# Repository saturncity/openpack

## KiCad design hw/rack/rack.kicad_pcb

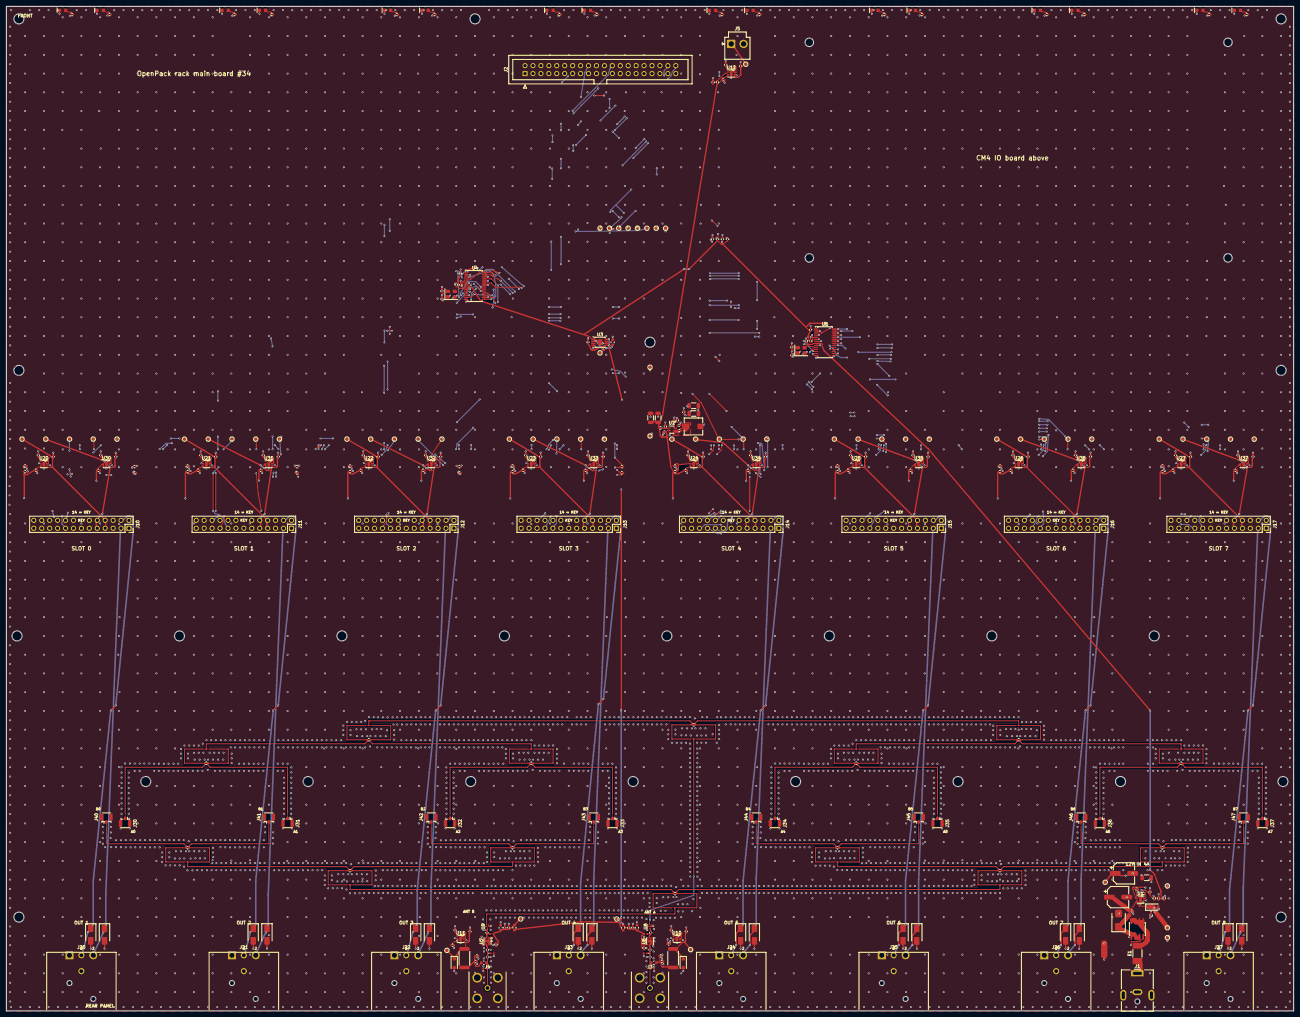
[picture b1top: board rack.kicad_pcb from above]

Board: 4 copper layers, 412.0 x 321.5 mm, 444 parts (0 on the bottom side), 251 nets.

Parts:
C1, C6: 100u 25V; CP_Elec_6.3x5.4
C2, C17, C30, C41, C50, C53, C56, C59, C62, C65, C68, C71, C74, C77, C80, C83, C86, C89, C92, C95: 22n; C_0402_1005Metric
C3, C8, C11, C14, C18, C20, C23, C24, C27, C31, C42, C51, C54, C57, C60, C63, C66, C69, C72, C75, C78, C81, C84, C87, C90, C93, C96: 100n; C_0402_1005Metric
C4, C15, C19, C32, C35, C43, C46, C52, C55, C58, C61, C64, C67, C70, C73, C76, C79, C82, C85, C88, C91, C94, C97: 1u; C_0402_1005Metric
C5, C9, C10: 10u 25V; C_1206_3216Metric
C7: 33n; C_0402_1005Metric
C12, C13: 22u 25V; C_1206_3216Metric
C16, C34, C45: 10u; C_0603_1608Metric
C21, C22, C25, C26: 33p; C_0402_1005Metric
C28, C33, C36, C37, C38, C39, C44, C47, C48, C49: 100p; C_0402_1005Metric
C29, C40: 10n; C_0402_1005Metric
D1: BZT52C12; D_SOD-123
D2: SMBJ12A; D_SMB
D3, D6: ESD103-B1-02EL; D_0402_1005Metric
D4, D7: SMF12A; D_SOD-123F
D5, D8: ESD101-B1-02EL; D_0402_1005Metric
D9, D13, D17, D21, D25, D29, D33, D37: green; LED_LiteOn_LTST-S270
D10, D14, D18, D22, D26, D30, D34, D38: red; LED_LiteOn_LTST-S270
D11, D12, D15, D16, D19, D20, D23, D24, D27, D28, D31, D32, D35, D36, D39, D40: SMAJ58CA; D_SMA
F1: 4A fast; Fuse_Littelfuse-NANO2-451_453
FB1, FB2: 600R@100M; L_0603_1608Metric
H1, H2, H3, H4, H5, H6, H7, H8: MountingHole_3.2mm_M3
HC0, HC1, HC2, HC3: MountingHole_2.7mm_M2.5
HS00, HS01, HS10, HS11, HS20, HS21, HS30, HS31, HS40, HS41, HS50, HS51, HS60, HS61, HS70, HS71: MountingHole_3.2mm_M3
J1: 12V IN; BarrelJack_CUI_PJ-063AH_Horizontal
J2: CM4IO J8; IDC-Header_2x20_P2.54mm_Vertical
J3: ANT A; BNC_TE_5415025-1_RA
J4: ANT B; BNC_TE_5415025-1_RA
J5: CM4IO 12V; JST_VH_B2P-VH_1x02_P3.96mm_Vertical
J10: SLOT 0; PinSocket_2x13_P2.54mm_Key14
J11: SLOT 1; PinSocket_2x13_P2.54mm_Key14
J12: SLOT 2; PinSocket_2x13_P2.54mm_Key14
J13: SLOT 3; PinSocket_2x13_P2.54mm_Key14
J14: SLOT 4; PinSocket_2x13_P2.54mm_Key14
J15: SLOT 5; PinSocket_2x13_P2.54mm_Key14
J16: SLOT 6; PinSocket_2x13_P2.54mm_Key14
J17: SLOT 7; PinSocket_2x13_P2.54mm_Key14
J20: OUT 1; Neutrik_NC3MAH
J21: OUT 2; Neutrik_NC3MAH
J22: OUT 3; Neutrik_NC3MAH
J23: OUT 4; Neutrik_NC3MAH
J24: OUT 5; Neutrik_NC3MAH
J25: OUT 6; Neutrik_NC3MAH
J26: OUT 7; Neutrik_NC3MAH
J27: OUT 8; Neutrik_NC3MAH
J30: RF A0; U.FL_Hirose_U.FL-R-SMT-1_Vertical
J31: RF A1; U.FL_Hirose_U.FL-R-SMT-1_Vertical
J32: RF A2; U.FL_Hirose_U.FL-R-SMT-1_Vertical
J33: RF A3; U.FL_Hirose_U.FL-R-SMT-1_Vertical
J34: RF A4; U.FL_Hirose_U.FL-R-SMT-1_Vertical
J35: RF A5; U.FL_Hirose_U.FL-R-SMT-1_Vertical
J36: RF A6; U.FL_Hirose_U.FL-R-SMT-1_Vertical
J37: RF A7; U.FL_Hirose_U.FL-R-SMT-1_Vertical
J40: RF B0; U.FL_Hirose_U.FL-R-SMT-1_Vertical
J41: RF B1; U.FL_Hirose_U.FL-R-SMT-1_Vertical
J42: RF B2; U.FL_Hirose_U.FL-R-SMT-1_Vertical
J43: RF B3; U.FL_Hirose_U.FL-R-SMT-1_Vertical
J44: RF B4; U.FL_Hirose_U.FL-R-SMT-1_Vertical
J45: RF B5; U.FL_Hirose_U.FL-R-SMT-1_Vertical
J46: RF B6; U.FL_Hirose_U.FL-R-SMT-1_Vertical
J47: RF B7; U.FL_Hirose_U.FL-R-SMT-1_Vertical
L1: 6.8u; L_Bourns_SRP5030T
L2, L4: 39n; L_0603_1608Metric
L3, L5: 18n; L_0402_1005Metric
NT1: GND-CHASSIS; NetTie-2_SMD_Pad2.0mm
Q1: AO4407A; SOIC-8_3.9x4.9mm_P1.27mm
R1, R3, R5, R11, R14, R16, R19, R32, R44, R52, R60, R68, R76, R82, R88, R94: 10k; R_0402_1005Metric
R2, R10, R43, R51, R59, R67, R75, R81, R87, R93: 73.2k; R_0402_1005Metric
R4: 576; R_0402_1005Metric
R6: 511k; R_0402_1005Metric
R7: 88.7k; R_0402_1005Metric
R8: 53.6k; R_0402_1005Metric
R9: 10.2k; R_0402_1005Metric
R12: 1.37k; R_0402_1005Metric
R13, R15, R48, R56, R64, R72: 1k; R_0402_1005Metric
R17, R30: 1; R_2512_6332Metric
R18, R31: 100k; R_0402_1005Metric
R20, R33, R45, R46, R53, R54, R61, R62, R69, R70, R77, R78, R83, R84, R89, R90, R95, R96: 4.42k; R_0402_1005Metric
R21, R34: 0; R_0402_1005Metric
R22, R35: 5.1k; R_0402_1005Metric
R23, R24, R25, R26, R27, R28, R29, R36, R37, R38, R39, R40, R41, R42, R47, R55, R63, R71: 100; R_0402_1005Metric
R49, R50, R57, R58, R65, R66, R73, R74, R79, R80, R85, R86, R91, R92, R97, R98: 560; R_0402_1005Metric
TL1, TL2, TL3, TL4, TL5, TL6, TL7, TL8, TL9, TL10, TL11, TL12, TL13, TL14, TL15, TL16, TL17, TL18, TL19, TL20, TL21, TL22, TL23, TL24, TL25, TL26, TL27, TL28: 70R7 L/4 18.02mm w0.170; Microstrip_NetTie
TL29, TL30, TL31, TL32, TL33, TL34, TL35, TL36, TL37, TL38, TL39, TL40, TL41, TL42, TL43, TL44: 50R feed; Microstrip_NetTie
TP1: +12V_PROT; TestPoint_Pad_D1.0mm
TP2: +12V_BUS; TestPoint_Pad_D1.0mm
TP3: +5V; TestPoint_Pad_D1.0mm
TP4: +3V3; TestPoint_Pad_D1.0mm
TP5: +12V_HOST; TestPoint_Pad_D1.0mm
TP6: HOST_GPIO6; TestPoint_Pad_D1.0mm
TP7, TP8, TP16: GND; TestPoint_Pad_D1.0mm
TP9: HOST_GPIO21; TestPoint_Pad_D1.0mm
TP10: HOST_GPIO20; TestPoint_Pad_D1.0mm
TP11: HOST_GPIO19; TestPoint_Pad_D1.0mm
TP12: HOST_GPIO18; TestPoint_Pad_D1.0mm
TP13: HOST_GPIO17; TestPoint_Pad_D1.0mm
TP14: HOST_GPIO24; TestPoint_Pad_D1.0mm
TP15: HOST_GPIO25; TestPoint_Pad_D1.0mm
TP17: BIAS_A_DC; TestPoint_Pad_D1.0mm
TP18: +5V_LNA_A; TestPoint_Pad_D1.0mm
TP19: BIAS_B_DC; TestPoint_Pad_D1.0mm
TP20: +5V_LNA_B; TestPoint_Pad_D1.0mm
TP21: +12V_S0; TestPoint_Pad_D1.0mm
TP22: +5V_S0; TestPoint_Pad_D1.0mm
TP23: S0_BP_UART_TX; TestPoint_Pad_D1.0mm
TP24: S0_BP_UART_RX; TestPoint_Pad_D1.0mm
TP25: S0_BP_nRESET; TestPoint_Pad_D1.0mm
TP26: +12V_S1; TestPoint_Pad_D1.0mm
TP27: +5V_S1; TestPoint_Pad_D1.0mm
TP28: S1_BP_UART_TX; TestPoint_Pad_D1.0mm
TP29: S1_BP_UART_RX; TestPoint_Pad_D1.0mm
TP30: S1_BP_nRESET; TestPoint_Pad_D1.0mm
TP31: +12V_S2; TestPoint_Pad_D1.0mm
TP32: +5V_S2; TestPoint_Pad_D1.0mm
TP33: S2_BP_UART_TX; TestPoint_Pad_D1.0mm
TP34: S2_BP_UART_RX; TestPoint_Pad_D1.0mm
TP35: S2_BP_nRESET; TestPoint_Pad_D1.0mm
TP36: +12V_S3; TestPoint_Pad_D1.0mm
TP37: +5V_S3; TestPoint_Pad_D1.0mm
TP38: S3_BP_UART_TX; TestPoint_Pad_D1.0mm
TP39: S3_BP_UART_RX; TestPoint_Pad_D1.0mm
TP40: S3_BP_nRESET; TestPoint_Pad_D1.0mm
TP41: +12V_S4; TestPoint_Pad_D1.0mm
TP42: +5V_S4; TestPoint_Pad_D1.0mm
TP43: S4_BP_UART_TX; TestPoint_Pad_D1.0mm
TP44: S4_BP_UART_RX; TestPoint_Pad_D1.0mm
TP45: S4_BP_nRESET; TestPoint_Pad_D1.0mm
TP46: +12V_S5; TestPoint_Pad_D1.0mm
TP47: +5V_S5; TestPoint_Pad_D1.0mm
TP48: S5_BP_UART_TX; TestPoint_Pad_D1.0mm
TP49: S5_BP_UART_RX; TestPoint_Pad_D1.0mm
TP50: S5_BP_nRESET; TestPoint_Pad_D1.0mm
TP51: +12V_S6; TestPoint_Pad_D1.0mm
TP52: +5V_S6; TestPoint_Pad_D1.0mm
TP53: S6_BP_UART_TX; TestPoint_Pad_D1.0mm
TP54: S6_BP_UART_RX; TestPoint_Pad_D1.0mm
TP55: S6_BP_nRESET; TestPoint_Pad_D1.0mm
TP56: +12V_S7; TestPoint_Pad_D1.0mm
TP57: +5V_S7; TestPoint_Pad_D1.0mm
TP58: S7_BP_UART_TX; TestPoint_Pad_D1.0mm
TP59: S7_BP_UART_RX; TestPoint_Pad_D1.0mm
TP60: S7_BP_nRESET; TestPoint_Pad_D1.0mm
U1, U10, U11, U12, U20, U21, U22, U23, U24, U25, U26, U27: TPS259541DSGR; Texas_DSG0008A_WSON-8-1EP_2x2mm_P0.5mm_EP0.9x1.6mm
U2: TPS62933DRLR; SOT-583-8
U3: TLV76733; HVSSOP-8-1EP_3x3mm_P0.65mm_EP1.57x1.89mm
U4, U5: SC16IS752IPW; TSSOP-28_4.4x9.7mm_P0.65mm
U6, U7: QPL9057; DFN-8-1EP_2x2mm_P0.5mm_EP0.9x1.6mm
U8, U9: QPQ1907; Qorvo_QPQ1907_LGA5_1.4x1.2mm_datasheet_land_pattern
U30, U31, U32, U33, U34, U35, U36, U37: TPS259531DSGR; Texas_DSG0008A_WSON-8-1EP_2x2mm_P0.5mm_EP0.9x1.6mm
Y1, Y2: 14.7456M; Crystal_SMD_3225-4Pin_3.2x2.5mm

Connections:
+3V3: C16.1, C23.1, C27.1, R5.1, R13.1, R14.1, R15.1, R16.1, R19.1, R32.1, TP4.1, U3.1, U3.2, U4.8, U5.8
+5V: C12.1, C13.1, C14.1, C15.1, C54.1, C60.1, C66.1, C72.1, C78.1, C84.1, C90.1, C96.1, FB1.1, FB2.1, L1.2, R8.1, TP3.1, U3.5, U3.8, U30.2, U30.3, U30.4, U31.2, U31.3, U31.4, U32.2, U32.3, U32.4, U33.2, U33.3, U33.4, U34.2, U34.3, U34.4, U35.2, U35.3, U35.4, U36.2, U36.3, U36.4, U37.2, U37.3, U37.4
+5V_LNA_A: C34.1, C35.1, C36.1, FB1.2, L3.1, R22.1, TP18.1
+5V_LNA_B: C45.1, C46.1, C47.1, FB2.2, L5.1, R35.1, TP20.1
+5V_S0: C55.1, J10.9, J10.10, TP22.1, U30.5
+5V_S1: C61.1, J11.9, J11.10, TP27.1, U31.5
+5V_S2: C67.1, J12.9, J12.10, TP32.1, U32.5
+5V_S3: C73.1, J13.9, J13.10, TP37.1, U33.5
+5V_S4: C79.1, J14.9, J14.10, TP42.1, U34.5
+5V_S5: C85.1, J15.9, J15.10, TP47.1, U35.5
+5V_S6: C91.1, J16.9, J16.10, TP52.1, U36.5
+5V_S7: C97.1, J17.9, J17.10, TP57.1, U37.5
+12V_BUS: C4.1, C5.1, C6.1, C9.1, C10.1, C11.1, C18.1, C31.1, C42.1, C51.1, C57.1, C63.1, C69.1, C75.1, C81.1, C87.1, C93.1, R2.1, R6.1, R10.1, R43.1, R51.1, R59.1, R67.1, R75.1, R81.1, R87.1, R93.1, TP2.1, U1.5, U2.3, U10.3, U10.4, U11.3, U11.4, U12.3, U12.4, U20.3, U20.4, U21.3, U21.4, U22.3, U22.4, U23.3, U23.4, U24.3, U24.4, U25.3, U25.4, U26.3, U26.4, U27.3, U27.4
+12V_HOST: C19.1, J5.1, TP5.1, U12.5
+12V_IN: F1.1, J1.1
+12V_PROT: C1.1, C3.1, D1.1, D2.1, Q1.1, Q1.2, Q1.3, TP1.1, U1.3, U1.4
+12V_RAW: F1.2, Q1.5, Q1.6, Q1.7, Q1.8
+12V_S0: C52.1, J10.7, J10.8, TP21.1, U20.5
+12V_S1: C58.1, J11.7, J11.8, TP26.1, U21.5
+12V_S2: C64.1, J12.7, J12.8, TP31.1, U22.5
+12V_S3: C70.1, J13.7, J13.8, TP36.1, U23.5
+12V_S4: C76.1, J14.7, J14.8, TP41.1, U24.5
+12V_S5: C82.1, J15.7, J15.8, TP46.1, U25.5
+12V_S6: C88.1, J16.7, J16.8, TP51.1, U26.5
+12V_S7: C94.1, J17.7, J17.8, TP56.1, U27.5
ANT_A: C33.1, D3.1, J3.1, L2.1
ANT_B: C44.1, D6.1, J4.1, L4.1
BIAS_A_DC: C32.1, D4.1, R17.2, TP17.1, U10.5
BIAS_A_RF: C28.1, C29.1, L2.2, R17.1
BIAS_B_DC: C43.1, D7.1, R30.2, TP19.1, U11.5
BIAS_B_RF: C39.1, C40.1, L4.2, R30.1
BUCK_BST: C8.1, U2.6
BUCK_EN: R6.2, R7.1, U2.2
BUCK_FB: R8.2, R9.1, U2.8
BUCK_SS: C7.1, U2.7
BUCK_SW: C8.2, L1.1, U2.5
CHASSIS: D11.2, D12.2, D15.2, D16.2, D19.2, D20.2, D23.2, D24.2, D27.2, D28.2, D31.2, D32.2, D35.2, D36.2, D39.2, D40.2, J20.1, J20.G, J21.1, J21.G, J22.1, J22.G, J23.1, J23.G, J24.1, J24.G, J25.1, J25.G, J26.1, J26.G, J27.1, J27.G, NT1.2
GND: C1.2, C2.2, C3.2, C4.2, C5.2, C6.2, C7.2, C9.2, C10.2, C11.2, C12.2, C13.2, C14.2, C15.2, C16.2, C17.2, C18.2, C19.2, C20.2, C21.2, C22.2, C23.2, C24.2, C25.2, C26.2, C27.2, C28.2, C29.2, C30.2, C31.2, C32.2, C34.2, C35.2, C36.2, C37.2, C39.2, C40.2, C41.2, C42.2, C43.2, C45.2, C46.2, C47.2, C48.2, C50.2, C51.2, C52.2, C53.2, C54.2, C55.2, C56.2, C57.2, C58.2, C59.2, C60.2, C61.2, C62.2, C63.2, C64.2, C65.2, C66.2, C67.2, C68.2, C69.2, C70.2, C71.2, C72.2, C73.2, C74.2, C75.2, C76.2, C77.2, C78.2, C79.2, C80.2, C81.2, C82.2, C83.2, C84.2, C85.2, C86.2, C87.2, C88.2, C89.2, C90.2, C91.2, C92.2, C93.2, C94.2, C95.2, C96.2, C97.2, D2.2, D3.2, D4.2, D5.2, D6.2, D7.2, D8.2, D9.1, D10.1, D13.1, D14.1, D17.1, D18.1, D21.1, D22.1, D25.1, D26.1, D29.1, D30.1, D33.1, D34.1, D37.1, D38.1, J1.2, J2.6, J2.9, J2.14, J2.20, J2.25, J2.30, J2.34, J2.39, J3.2, J4.2, J5.2, J10.1, J10.2, J10.5, J10.6, J10.11, J10.12, J10.23, J10.24, J10.25, J10.26, J11.1, J11.2, J11.5, J11.6, J11.11, J11.12, J11.24, J11.25, J11.26, J12.1, J12.2, J12.5, J12.6, J12.11, J12.12, J12.23, J12.25, J12.26, J13.1, J13.2, J13.5, J13.6, J13.11, J13.12, J13.25, J13.26, J14.1, J14.2, J14.5, J14.6, J14.11, J14.12, J14.23, J14.24, J14.26, J15.1, J15.2, J15.5, J15.6, J15.11, J15.12, J15.24, J15.26, J16.1, J16.2, J16.5, J16.6, J16.11, J16.12, J16.23, J16.26, J17.1, J17.2, J17.5, J17.6, J17.11, J17.12, J17.26, J30.2, J31.2, J32.2, J33.2, J34.2, J35.2, J36.2, J37.2, J40.2, J41.2, J42.2, J43.2, J44.2, J45.2, J46.2, J47.2, NT1.1, R1.2, R3.2, R4.2, R7.2, R9.2, R11.2, R12.2, R18.2, R20.2, R31.2, R33.2, R44.2, R45.2, R46.2, R52.2, R53.2, R54.2, R60.2, R61.2, R62.2, R68.2, R69.2, R70.2, R76.2, R77.2, R78.2, R82.2, R83.2, R84.2, R88.2, R89.2, R90.2, R94.2, R95.2, R96.2, TP7.1, TP8.1, TP16.1, U1.8, U1.9, U2.4, U3.4, U3.6, U3.9, U4.2, U4.9, U4.14, U4.16, U4.22, U5.2, U5.9, U5.14, U5.16, U5.22, U6.3, U6.4, U6.5, U6.6, U6.8, U6.9, U7.3, U7.4, U7.5, U7.6, U7.8, U7.9, U8.2, U8.3, U8.5, U9.2, U9.3, U9.5, U10.8, U10.9, U11.8, U11.9, U12.8, U12.9, U20.8, U20.9, U21.8, U21.9, U22.8, U22.9, U23.8, U23.9, U24.8, U24.9, U25.8, U25.9, U26.8, U26.9, U27.8, U27.9, U30.8, U30.9, U31.8, U31.9, U32.8, U32.9, U33.8, U33.9, U34.8, U34.9, U35.8, U35.9, U36.8, U36.9, U37.8, U37.9
HOST_GPIO4: J2.7, R55.1
HOST_GPIO5: J2.29, R56.2
HOST_GPIO6: J2.31, R5.2, TP6.1, U1.6, U12.6, U20.6, U21.6, U22.6, U23.6, U24.6, U25.6, U26.6, U27.6, U30.6, U31.6, U32.6, U33.6, U34.6, U35.6, U36.6, U37.6
HOST_GPIO8: J2.24, R63.1
HOST_GPIO9: J2.21, R64.2
HOST_GPIO12: J2.32, R71.1
HOST_GPIO13: J2.33, R72.2
HOST_GPIO14: J2.8, R47.1
HOST_GPIO15: J2.10, R48.2
HOST_GPIO17: J2.11, TP13.1, U5.10
HOST_GPIO18: J2.12, TP12.1, U4.10
HOST_GPIO19: J2.35, TP11.1, U4.12, U5.12
HOST_GPIO20: J2.38, TP10.1, U4.11, U5.11
HOST_GPIO21: J2.40, TP9.1, U4.13, U5.13
HOST_GPIO22: J2.15, R18.1, U10.2
HOST_GPIO23: J2.16, R31.1, U11.2
HOST_GPIO24: J2.18, R13.2, TP14.1, U4.15
HOST_GPIO25: J2.22, R15.2, TP15.1, U5.15
HOST_GPIO26: J2.37, R19.2, U10.6
HOST_GPIO27: J2.13, R32.2, U11.6
LNA_A_IN: C33.2, D5.1, R21.1
LNA_A_OUT: C38.2, U8.1
LNA_A_RFIN: R21.2, U6.2
LNA_A_RFOUT: C38.1, L3.2, U6.7
LNA_A_VBIAS: C37.1, R22.2, U6.1
LNA_B_IN: C44.2, D8.1, R34.1
LNA_B_OUT: C49.2, U9.1
LNA_B_RFIN: R34.2, U7.2
LNA_B_RFOUT: C49.1, L5.2, U7.7
LNA_B_VBIAS: C48.1, R35.2, U7.1
Q1_G: D1.2, Q1.4, R1.1
RF_A0: J30.1, TL29.2
RF_A1: J31.1, TL31.2
RF_A2: J32.1, TL33.2
RF_A3: J33.1, TL35.2
RF_A4: J34.1, TL37.2
RF_A5: J35.1, TL39.2
RF_A6: J36.1, TL41.2
RF_A7: J37.1, TL43.2
RF_B0: J40.1, TL30.2
RF_B1: J41.1, TL32.2
RF_B2: J42.1, TL34.2
RF_B3: J43.1, TL36.2
RF_B4: J44.1, TL38.2
RF_B5: J45.1, TL40.2
RF_B6: J46.1, TL42.2
RF_B7: J47.1, TL44.2
S0_AUD_COLD: D12.1, J10.4, J20.3
S0_AUD_HOT: D11.1, J10.3, J20.2
S0_BP_BOOT: J10.20, U4.19
S0_BP_LED_LOCK: J10.21, R49.1
S0_BP_LED_LOCK_A: D9.2, R49.2
S0_BP_LED_PEAK: J10.22, R50.1
S0_BP_LED_PEAK_A: D10.2, R50.2
S0_BP_UART_RX: J10.18, R47.2, TP24.1
S0_BP_UART_TX: J10.17, R48.1, TP23.1
S0_BP_nRESET: J10.19, TP25.1, U4.18
S1_AUD_COLD: D16.1, J11.4, J21.3
S1_AUD_HOT: D15.1, J11.3, J21.2
S1_BP_BOOT: J11.20, U4.21
S1_BP_LED_LOCK: J11.21, R57.1
S1_BP_LED_LOCK_A: D13.2, R57.2
S1_BP_LED_PEAK: J11.22, R58.1
S1_BP_LED_PEAK_A: D14.2, R58.2
S1_BP_UART_RX: J11.18, R55.2, TP29.1
S1_BP_UART_TX: J11.17, R56.1, TP28.1
S1_BP_nRESET: J11.19, TP30.1, U4.20
S2_AUD_COLD: D20.1, J12.4, J22.3
S2_AUD_HOT: D19.1, J12.3, J22.2
S2_BP_BOOT: J12.20, U4.26
S2_BP_LED_LOCK: J12.21, R65.1
S2_BP_LED_LOCK_A: D17.2, R65.2
S2_BP_LED_PEAK: J12.22, R66.1
S2_BP_LED_PEAK_A: D18.2, R66.2
S2_BP_UART_RX: J12.18, R63.2, TP34.1
S2_BP_UART_TX: J12.17, R64.1, TP33.1
S2_BP_nRESET: J12.19, TP35.1, U4.25
S3_AUD_COLD: D24.1, J13.4, J23.3
S3_AUD_HOT: D23.1, J13.3, J23.2
S3_BP_BOOT: J13.20, U4.28
S3_BP_LED_LOCK: J13.21, R73.1
S3_BP_LED_LOCK_A: D21.2, R73.2
S3_BP_LED_PEAK: J13.22, R74.1
S3_BP_LED_PEAK_A: D22.2, R74.2
S3_BP_UART_RX: J13.18, R71.2, TP39.1
S3_BP_UART_TX: J13.17, R72.1, TP38.1
S3_BP_nRESET: J13.19, TP40.1, U4.27
S4_AUD_COLD: D28.1, J14.4, J24.3
S4_AUD_HOT: D27.1, J14.3, J24.2
S4_BP_BOOT: J14.20, U5.19
S4_BP_LED_LOCK: J14.21, R79.1
S4_BP_LED_LOCK_A: D25.2, R79.2
S4_BP_LED_PEAK: J14.22, R80.1
S4_BP_LED_PEAK_A: D26.2, R80.2
S4_BP_UART_RX: J14.18, TP44.1, U4.3
S4_BP_UART_TX: J14.17, TP43.1, U4.4
S4_BP_nRESET: J14.19, TP45.1, U5.18
S5_AUD_COLD: D32.1, J15.4, J25.3
S5_AUD_HOT: D31.1, J15.3, J25.2
S5_BP_BOOT: J15.20, U5.21
S5_BP_LED_LOCK: J15.21, R85.1
S5_BP_LED_LOCK_A: D29.2, R85.2
S5_BP_LED_PEAK: J15.22, R86.1
S5_BP_LED_PEAK_A: D30.2, R86.2
S5_BP_UART_RX: J15.18, TP49.1, U4.23
S5_BP_UART_TX: J15.17, TP48.1, U4.24
S5_BP_nRESET: J15.19, TP50.1, U5.20
S6_AUD_COLD: D36.1, J16.4, J26.3
S6_AUD_HOT: D35.1, J16.3, J26.2
S6_BP_BOOT: J16.20, U5.26
S6_BP_LED_LOCK: J16.21, R91.1
S6_BP_LED_LOCK_A: D33.2, R91.2
S6_BP_LED_PEAK: J16.22, R92.1
S6_BP_LED_PEAK_A: D34.2, R92.2
S6_BP_UART_RX: J16.18, TP54.1, U5.3
S6_BP_UART_TX: J16.17, TP53.1, U5.4
S6_BP_nRESET: J16.19, TP55.1, U5.25
S7_AUD_COLD: D40.1, J17.4, J27.3
S7_AUD_HOT: D39.1, J17.3, J27.2
S7_BP_BOOT: J17.20, U5.28
S7_BP_LED_LOCK: J17.21, R97.1
S7_BP_LED_LOCK_A: D37.2, R97.2
S7_BP_LED_PEAK: J17.22, R98.1
S7_BP_LED_PEAK_A: D38.2, R98.2
S7_BP_UART_RX: J17.18, TP59.1, U5.23
S7_BP_UART_TX: J17.17, TP58.1, U5.24
S7_BP_nRESET: J17.19, TP60.1, U5.27
SPL_A_IN: TL1.1, TL2.1, U8.4
SPL_B_IN: TL15.1, TL16.1, U9.4
U1_DVDT: C2.1, U1.1
U1_EN: R2.2, R3.1, U1.2
U1_ILM: R4.1, U1.7
U4_RST: C20.1, R14.2, U4.5
U4_XTAL1: C21.1, U4.6, Y1.1
U4_XTAL2: C22.1, U4.7, Y1.2
U5_RST: C24.1, R16.2, U5.5
U5_XTAL1: C25.1, U5.6, Y2.1
U5_XTAL2: C26.1, U5.7, Y2.2
U10_DVDT: C30.1, U10.1
U10_ILM: R20.1, U10.7
U11_DVDT: C41.1, U11.1
U11_ILM: R33.1, U11.7
U12_DVDT: C17.1, U12.1
U12_EN: R10.2, R11.1, U12.2
U12_ILM: R12.1, U12.7
U20_DVDT: C50.1, U20.1
U20_EN: R43.2, R44.1, U20.2
U20_ILM: R45.1, U20.7
U21_DVDT: C56.1, U21.1
U21_EN: R51.2, R52.1, U21.2
U21_ILM: R53.1, U21.7
U22_DVDT: C62.1, U22.1
U22_EN: R59.2, R60.1, U22.2
U22_ILM: R61.1, U22.7
U23_DVDT: C68.1, U23.1
U23_EN: R67.2, R68.1, U23.2
U23_ILM: R69.1, U23.7
U24_DVDT: C74.1, U24.1
U24_EN: R75.2, R76.1, U24.2
U24_ILM: R77.1, U24.7
U25_DVDT: C80.1, U25.1
U25_EN: R81.2, R82.1, U25.2
U25_ILM: R83.1, U25.7
U26_DVDT: C86.1, U26.1
U26_EN: R87.2, R88.1, U26.2
U26_ILM: R89.1, U26.7
U27_DVDT: C92.1, U27.1
U27_EN: R93.2, R94.1, U27.2
U27_ILM: R95.1, U27.7
U30_DVDT: C53.1, U30.1
U30_ILM: R46.1, U30.7
U31_DVDT: C59.1, U31.1
U31_ILM: R54.1, U31.7
U32_DVDT: C65.1, U32.1
U32_ILM: R62.1, U32.7
U33_DVDT: C71.1, U33.1
U33_ILM: R70.1, U33.7
U34_DVDT: C77.1, U34.1
U34_ILM: R78.1, U34.7
U35_DVDT: C83.1, U35.1
U35_ILM: R84.1, U35.7
U36_DVDT: C89.1, U36.1
U36_ILM: R90.1, U36.7
U37_DVDT: C95.1, U37.1
U37_ILM: R96.1, U37.7
WK_A_10a: R23.1, TL1.2, TL3.1, TL4.1
WK_A_10b: R23.2, TL2.2, TL5.1, TL6.1
WK_A_20a: R24.1, TL3.2, TL7.1, TL8.1
WK_A_20b: R24.2, TL4.2, TL9.1, TL10.1
WK_A_21a: R25.1, TL5.2, TL11.1, TL12.1
WK_A_21b: R25.2, TL6.2, TL13.1, TL14.1
WK_A_30a: R26.1, TL7.2, TL29.1
WK_A_30b: R26.2, TL8.2, TL31.1
WK_A_31a: R27.1, TL9.2, TL33.1
WK_A_31b: R27.2, TL10.2, TL35.1
WK_A_32a: R28.1, TL11.2, TL37.1
WK_A_32b: R28.2, TL12.2, TL39.1
WK_A_33a: R29.1, TL13.2, TL41.1
WK_A_33b: R29.2, TL14.2, TL43.1
WK_B_10a: R36.1, TL15.2, TL17.1, TL18.1
WK_B_10b: R36.2, TL16.2, TL19.1, TL20.1
WK_B_20a: R37.1, TL17.2, TL21.1, TL22.1
WK_B_20b: R37.2, TL18.2, TL23.1, TL24.1
WK_B_21a: R38.1, TL19.2, TL25.1, TL26.1
WK_B_21b: R38.2, TL20.2, TL27.1, TL28.1
WK_B_30a: R39.1, TL21.2, TL30.1
WK_B_30b: R39.2, TL22.2, TL32.1
WK_B_31a: R40.1, TL23.2, TL34.1
WK_B_31b: R40.2, TL24.2, TL36.1
WK_B_32a: R41.1, TL25.2, TL38.1
WK_B_32b: R41.2, TL26.2, TL40.1
WK_B_33a: R42.1, TL27.2, TL42.1
WK_B_33b: R42.2, TL28.2, TL44.1

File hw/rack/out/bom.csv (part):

refs,qty,value,mpn,unit_gbp,ext_gbp,qty_break,uk_distributor,source
C1 C6,2,100u 25V,ALU_100u_25V,0.080,0.16,1,LCSC,est. (as hw/rx/prices.py)
C2 C17 C30 C41 C50 C53 C56 C59 C62 C65 C68 C71 C74 C77 C80 C83 C86 C89 C92 C95,20,22n,C_22n_0402,0.020,0.40,10,LCSC,est.
C3 C8 C11 C14 C18 C20 C23 C24 C27 C31 C42 C51 C54 C57 C60 C63 C66 C69 C72 C75 C78 C81 C84 C87 C90 C93 C96,27,100n,C_100n_0402,0.020,0.54,10,LCSC,est.
C4 C15 C19 C32 C35 C43 C46 C52 C55 C58 C61 C64 C67 C70 C73 C76 C79 C82 C85 C88 C91 C94 C97,23,1u,C_1u_0402,0.020,0.46,10,LCSC,est.
C5 C9 C10,3,10u 25V,C_10u_1206_25V_X7R,0.090,0.27,1,LCSC,"est. (as hw/rx/prices.py, USD 0.12)"
C7,1,33n,C_33n_0402,0.020,0.02,10,LCSC,est.
C12 C13,2,22u 25V,C_22u_1206_25V_X5R,0.100,0.20,1,LCSC,est.
C16 C34 C45,3,10u,C_10u_0603_X5R,0.050,0.15,10,LCSC,est.
C21 C22 C25 C26,4,33p,C_33p_0402_C0G,0.020,0.08,10,LCSC,est.
C28 C33 C36 C37 C38 C39 C44 C47 C48 C49,10,100p,C_100p_0402_C0G,0.020,0.20,10,LCSC,est.
C29 C40,2,10n,C_10n_0402,0.020,0.04,10,LCSC,est.
D1,1,BZT52C12,BZT52C12,0.030,0.03,1,LCSC,est. (12 V zener SOD-123)
D2,1,SMBJ12A,SMBJ12A,0.370,0.37,1,DigiKey UK,"DigiKey UK 2026-11-01, read (Littelfuse)"
D3 D6,2,ESD103-B1-02EL,ESD103-B1-02EL,0.300,0.60,1,Farnell UK / LCSC,"est. (Infineon 15 V 0.09 pF RF ESD, TSLP-2-20; Farnell UK 2725731, LCSC C535146)"
D4 D7,2,SMF12A,SMF12A,0.080,0.16,1,LCSC / Farnell UK,est. (SMF 200 W TVS SOD-123F)
D5 D8,2,ESD101-B1-02EL,ESD101-B1-02EL,0.300,0.60,1,Farnell UK,"est. (Infineon 5.5 V 0.1 pF RF ESD, TSLP-2-20; Farnell UK 2480926)"
D9 D13 D17 D21 D25 D29 D33 D37,8,green,LTST-S270KGKT,0.030,0.24,1,LCSC,"est. (Lite-On side-looking green, LCSC C125113, USD 0.042, JLC parts record 2026-11-01 (stock unconfirmed))"
D10 D14 D18 D22 D26 D30 D34 D38,8,red,LTST-S270KRKT,0.030,0.24,1,LCSC,"est. (Lite-On side-looking red, LCSC C125114, USD 0.032, JLC parts record 2026-11-01 (stock unconfirmed))"
D11 D12 D15 D16 D19 D20 D23 D24 D27 D28 D31 D32 D35 D36 D39 D40,16,SMAJ58CA,SMAJ58CA,0.360,5.76,1,DigiKey UK,"DigiKey UK 2026-11-01, read (Littelfuse)"
F1,1,4A fast,0451004.MRL,0.900,0.90,1,LCSC,"est. (Littelfuse Nano2 451 4 A fast 125 V, 2410 case 6.1 x 2.5 mm, LCSC C27515 (LCSC record read 2026-11-01); footprint Fuse_Littelfuse-NANO2-451_453 = the 2410 land)"
FB1 FB2,2,600R@100M,FB_0603_600R,0.030,0.06,10,LCSC,est. (Murata BLM18KG601SN1D 600 ohm 1.3 A 0603; LCSC C85833)
J1,1,12V IN,PJ-063AH,1.220,1.22,1,DigiKey UK,"DigiKey UK 2026-11-01, read (CUI / Same Sky PJ-063AH 2.1 mm 8 A, 34,138 in stock; not locking): buy UK"
J2,1,CM4IO J8,2.54-2*20P,0.100,0.10,1,LCSC,"est. (BOOMELE 2x20 2.54 mm IDC header, LCSC C9138, LCSC record read 2026-11-01)"
J3 J4,2,ANT A,5415025-1,6.950,13.90,1,DigiKey UK / Mouser UK,"est. (TE right-angle PCB BNC 50 ohm 4 GHz, 1/2-28 bulkhead; buy UK: DigiKey UK / Mouser UK, LCSC C5164649 USD 9.15 for reference; Molex 73138-5033 is the drop-in alternative)"
J5,1,CM4IO 12V,B2P-VH,0.150,0.15,1,LCSC,"est. (JST B2P-VH 2-pin 3.96 mm header, CM4IO 12 V feed; LCSC C160315)"
J10 J11 J12 J13 J14 J15 J16 J17,8,SLOT 0,2.54-2*13PFemale,0.170,1.36,1,LCSC,"est. (BOOMELE 2x13 2.54 mm female 8.5 mm, LCSC C64320, USD 0.2225, JLC parts record 2026-11-01 (stock unconfirmed)); contact 14 pulled and the cavity plugged at assembly: the footprint has no hole at 14 (ADR-0014 key)"
J20 J21 J22 J23 J24 J25 J26 J27,8,OUT 1,NC3MAH,2.080,16.64,1,LCSC / DigiKey UK,"DigiKey UK 2026-11-01, read (Neutrik NC3MAH; the LCSC buy is C5154126, Extended, price there unconfirmed)"
J30 J31 J32 J33 J34 J35 J36 J37 J40 J41 J42 J43 J44 J45 J46 J47,16,RF A0,U.FL-R-SMT-1(10),0.340,5.44,10,LCSC,"est. (Hirose U.FL-R-SMT-1(10), LCSC C88373 (not C88374))"
L1,1,6.8u,SRP5030T-6R8M,0.620,0.62,1,DigiKey UK / Mouser UK / Farnell UK,"est. (Bourns SRP5030T-6R8M 6.8 uH, Irms 4.0 A, Isat 4.3 A, DCR 76.2 mohm, Bourns datasheet read 2026-11-01; buy UK, not LCSC: C177249 is only 3.5 A)"
L2 L4,2,39n,CS0603-39NJ-S,0.020,0.04,10,LCSC,"est. (Chilisin 39 nH 5 % 0603, SRF 2.2 GHz, Q 40, 600 mA, DCR 0.25 ohm; LCSC C142171, LCSC record read 2026-11-01)"
L3 L5,2,18n,SDWL1005C18NGSTF,0.020,0.04,10,LCSC,"est. (Sunlord 18 nH 2 % 0402, SRF 4.5 GHz; LCSC C361616, LCSC record read 2026-11-01)"
NT1,1,GND-CHASSIS,R_0402_0R,0.010,0.01,1,LCSC,est.
Q1,1,AO4407A,AO4407A,0.250,0.25,1,LCSC,est. (Alpha & Omega -30 V 12 A P-FET SO-8; DMP3013SFV-7 is 0-stock at DigiKey UK)
R1 R3 R5 R11 R14 R16 R19 R32 R44 R52 R60 R68 R76 R82 R88 R94,16,10k,R_0402_1%,0.010,0.16,10,LCSC,est.
R2 R10 R43 R51 R59 R67 R75 R81 R87 R93,10,73.2k,R_0402_1%,0.010,0.10,10,LCSC,est.
R4,1,576,R_0402_1%,0.010,0.01,10,LCSC,est.
R6,1,511k,R_0402_1%,0.010,0.01,10,LCSC,est.
R7,1,88.7k,R_0402_1%,0.010,0.01,10,LCSC,est.
R8,1,53.6k,R_0402_1%,0.010,0.01,10,LCSC,est.
R9,1,10.2k,R_0402_1%,0.010,0.01,10,LCSC,est.
R12,1,1.37k,R_0402_1%,0.010,0.01,10,LCSC,est.
R13 R15 R48 R56 R64 R72,6,1k,R_0402_1%,0.010,0.06,10,LCSC,est.
R17 R30,2,1,R_2512_1R_1W,0.100,0.20,1,LCSC / Farnell UK,est. (1 ohm 1 % 2512 1 W thick film)
R18 R31,2,100k,R_0402_1%,0.010,0.02,10,LCSC,est.
R20 R33 R45 R46 R53 R54 R61 R62 R69 R70 R77 R78 R83 R84 R89 R90 R95 R96,18,4.42k,R_0402_1%,0.010,0.18,10,LCSC,est.
R21 R34,2,0,R_0402_0R,0.010,0.02,1,LCSC,est.
R22 R35,2,5.1k,R_0402_1%,0.010,0.02,10,LCSC,est.
R23 R24 R25 R26 R27 R28 R29 R36 R37 R38 R39 R40 R41 R42,14,100,R_0402_100R_TF,0.080,1.12,10,LCSC / Farnell UK,"est. (100 ohm 0402 thin film, Wilkinson isolation)"
R47 R55 R63 R71,4,100,R_0402_1%,0.010,0.04,10,LCSC,est.
R49 R50 R57 R58 R65 R66 R73 R74 R79 R80 R85 R86 R91 R92 R97 R98,16,560,R_0402_1%,0.010,0.16,10,LCSC,est.
TL1 TL2 TL3 TL4 TL5 TL6 TL7 TL8 TL9 TL10 TL11 TL12 TL13 TL14 TL15 TL16 TL17 TL18 TL19 TL20 TL21 TL22 TL23 TL24 TL25 TL26 TL27 TL28,28,70R7 L/4 18.02mm w0.170,PCB_TRACE,0.000,0.00,1,-,copper on the main board (hw/rack/wilkinson.py): no part
TL29 TL30 TL31 TL32 TL33 TL34 TL35 TL36 TL37 TL38 TL39 TL40 TL41 TL42 TL43 TL44,16,50R feed,PCB_TRACE,0.000,0.00,1,-,copper on the main board (hw/rack/wilkinson.py): no part
TP1 TP2 TP3 TP4 TP5 TP6 TP7 TP8 TP9 TP10 TP11 TP12 TP13 TP14 TP15 TP16 TP17 TP18 TP19 TP20 TP21 TP22 TP23 TP24 TP25 TP26 TP27 TP28 TP29 TP30 TP31 TP32 TP33 TP34 TP35 TP36 TP37 TP38 TP39 TP40 TP41 TP42 TP43 TP44 TP45 TP46 TP47 TP48 TP49 TP50 TP51 TP52 TP53 TP54 TP55 TP56 TP57 TP58 TP59 TP60,60,+12V_PROT,TP-pad,0.000,0.00,1,-,est. (footprint only: bare test pad)
U1 U10 U11 U12 U20 U21 U22 U23 U24 U25 U26 U27,12,TPS259541DSGR,TPS259541DSGR,0.558,6.70,10,DigiKey UK,"DigiKey UK 2026-11-01, read qty-10 break; 20-week lead, stock not shown"
U2,1,TPS62933DRLR,TPS62933DRLR,1.200,1.20,1,DigiKey UK / Farnell UK,"est. (TI TPS62933 3 A buck, SOT-583)"
U3,1,TLV76733,TLV76733DGNR,0.300,0.30,1,Farnell UK / DigiKey UK / Mouser UK,"est. (as hw/rx/prices.py, USD 0.40)"
U4 U5,2,SC16IS752IPW,"SC16IS752IPW,128",5.920,11.84,1,DigiKey UK,"DigiKey UK 2026-11-01, read (11,036 in stock); the ,112 tube variant is obsolete"
U6 U7,2,QPL9057,QPL9057TR7,4.600,9.20,1,DigiKey UK,"DigiKey UK 2026-11-01, read (61,763 in stock); 25+ GBP 3.77, 100+ GBP 3.17"
U8 U9,2,QPQ1907,QPQ1907SR,2.820,5.64,1,DigiKey UK,"DigiKey UK 2026-11-01, read (7,548 in stock; 33-week lead); IL 1.3 typ / 2.2 max dB"
U30 U31 U32 U33 U34 U35 U36 U37,8,TPS259531DSGR,TPS259531DSGR,0.558,4.46,10,DigiKey UK,"DigiKey UK 2026-11-01, read qty-10 break (4,178 in stock)"
Y1 Y2,2,14.7456M,XC32M4-14.7456-F20NLDTL,0.060,0.12,1,LCSC,"LCSC C3034317 read via the JLC parts API: HCI 14.7456 MHz 3225 20 pF, ESR 60 ohm, -40..+85 C, 10 ppm (LCSC C3034317, USD 0.0814, JLC parts record read 2026-11-01, 6,684 in stock; #126 review: replaces the 100 ohm AKER C6523919)"
-,1,"Raspberry Pi CM4 2 GB RAM / 8 GB eMMC, no wireless (SC0680 = CM4002008)",-,79.200,79.20,1,The Pi Hut UK,"The Pi Hut UK, qty 1, 2026-11-01 (coordinator decision on #95; DigiKey UK SC0680 was 0 stock at GBP 61.64). SC0681 (16 GB eMMC) same price is the drop-in alternative"
-,1,Raspberry Pi CM4 IO Board (SC0326),-,26.150,26.15,1,DigiKey UK,"DigiKey UK 2026-11-01, read"
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
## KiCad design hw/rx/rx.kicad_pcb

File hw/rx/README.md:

# hw/rx

Receiver sub-board (one per pack, eight per rack), captured in SKiDL (`rx.py`). Decisions: ADR-0021 (module: BT40E, no FEM; the pack keeps ADR-0007's BT40NE), ADR-0011 (antenna logic), ADR-0014 (this board: backplane pinout, GPIO map, DAC, balanced driver).

- `python hw/rx/rx.py` (venv with `skidl==3.0.0`) runs ERC, then writes `out/rx.net` (KiCad netlist), `out/bom.csv` (USD + GBP + UK distributor per line, printed by `audit.py`), `out/sch/*.kicad_sch` (KiCad 9, one sheet per block: power, mcu, rf, dac, driver) and `out/svg/*.svg`. `--no-sch` skips the schematic render.
- `symbols_rx.py` writes `openpack_rx.kicad_sym` (the pack's symbols plus PCM5102A, PE4259, U.FL, BAV99, TVS, backplane header). `prices.py` holds qty-100 prices with sources.
- Checks: `tests/test_rx_sch.py` (ERC 0/0, BOM current, UART/I2S/ANT_SEL pads, straps, polarity, backplane pinout = ADR table) and `tests/test_spice_rx_driver.py` (`hw/spice/rx_driver.cir`: level, headroom, flatness, CM and swing vs rails, Zout, hum, noise; `rx_driver_load.cir`: phase margin and step into 10 nF + 600 ohm, phantom short; `rx_driver_power.cir`: power cycle through the mute relay).

## PCB (#34)

- `python3 hw/rx/layout_rx.py` (system python with KiCad 10 `pcbnew`): `out/rx.net` → placement → RF pre-route + via fence → GND fan-out → routing (the pack's `hw/pack/router.py`) → pours → `kicad-cli` DRC (refill saved) → `outputs_rx.py` (gerbers, drill, `bom_jlc.csv`, `cpl_jlc.csv`, `rx.step`, `mech.json`, renders of every layer). About 40 s.
- `footprints_rx.py` writes `openpack.pretty` (BT40E from Fanstel p.11, TQ2SA, land pattern provisional). `rf_line.py` is the 2D field solve behind the 0.31 mm / 0.25 mm 50 Ω line (needs the `.ws` venv for numpy/scipy). `rx.kicad_dru` holds the JLC rules.
- Checks: `tests/test_rx_layout.py` (CI `pcb` job). The review is the receiver section of `hw/REVIEW.md`.

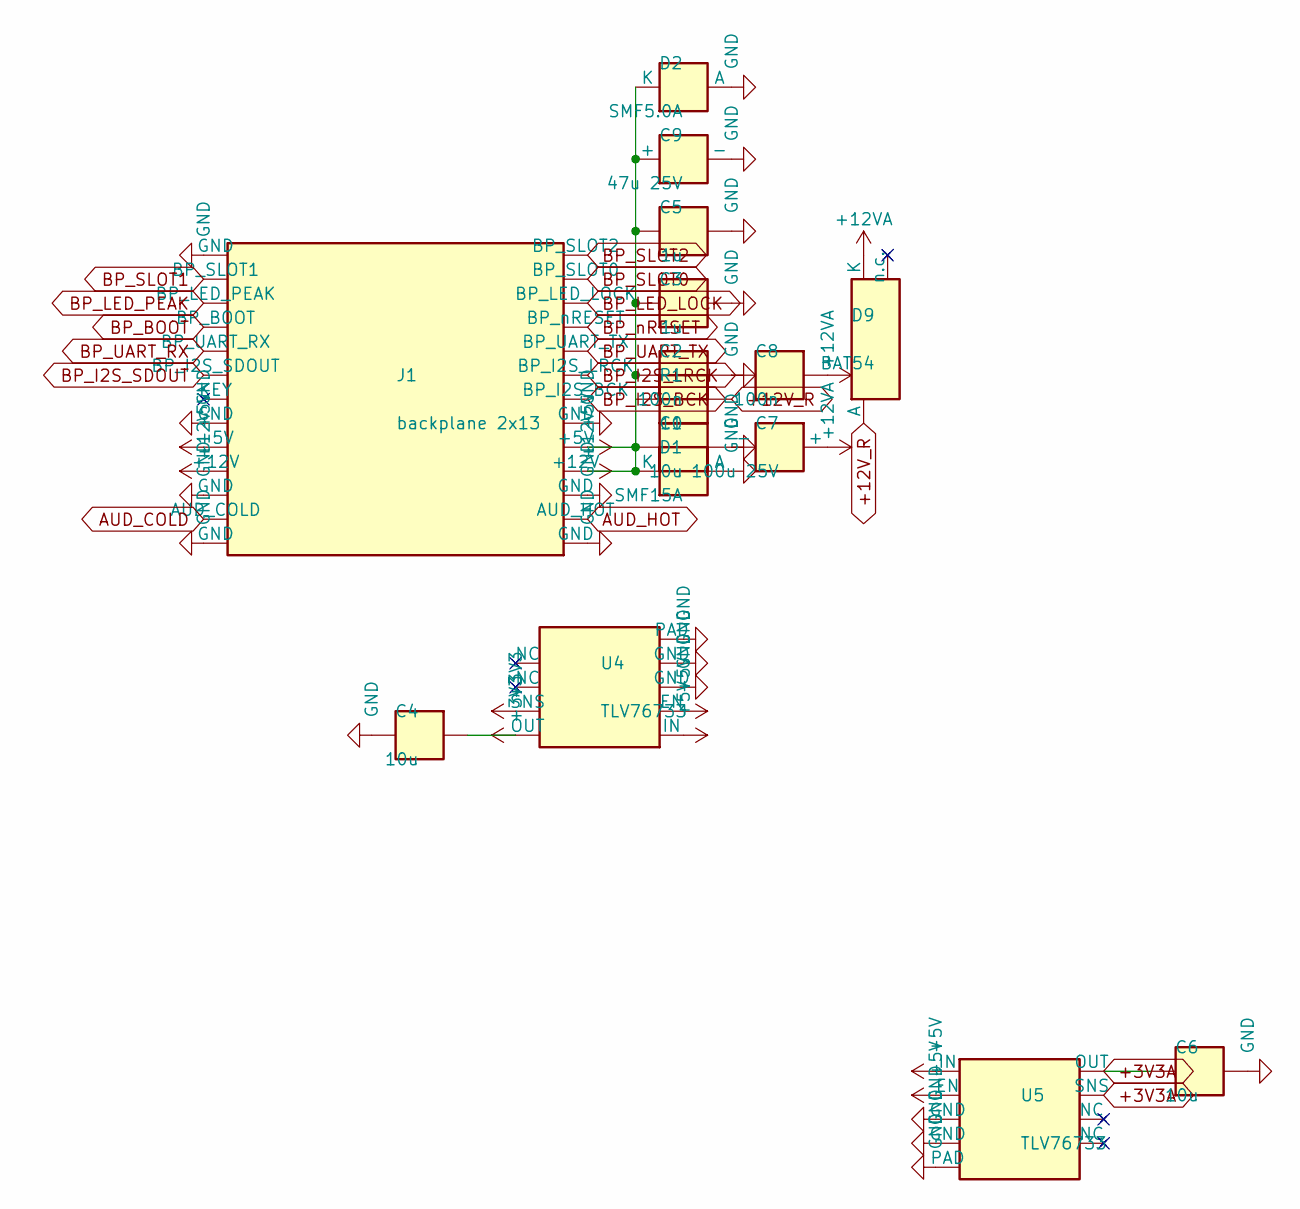
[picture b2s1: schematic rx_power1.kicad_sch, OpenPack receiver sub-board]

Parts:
C1, C4, C6: 10u; C_0603_1608Metric; MPN C_10u_0603_X5R
C2, C8: 100n; C_0402_1005Metric; MPN C_100n_0402
C3, C5: 1u; C_0402_1005Metric; MPN C_1u_0402
C7: 100u 25V; CP_Elec_6.3x5.4; MPN ALU_100u_25V
C9: 47u 25V; CP_Elec_5x5.4; MPN ALU_47u_25V
D1: SMF15A; D_SOD-123F; MPN SMF15A
D2: SMF5.0A; D_SOD-123F; MPN SMF5.0A
D9: BAT54; SOT-23; MPN BAT54,215
J1: backplane 2x13; PinHeader_2x13_P2.54mm_Key14; MPN PZ254V-12-26P
R1: 10; R_0603_1608Metric; MPN R_0603_1%
U4, U5: TLV76733; HVSSOP-8-1EP_3x3mm_P0.65mm_EP1.57x1.89mm; MPN TLV76733DGNR

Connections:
+3V3A: C6.1, U5.1 (OUT), U5.2 (SNS); also elsewhere on the board
+12V_R: D9.1 (A), R1.2
AUD_COLD: J1.4 (AUD_COLD); also elsewhere on the board
AUD_HOT: J1.3 (AUD_HOT); also elsewhere on the board
BP_BOOT: J1.20 (BP_BOOT); also elsewhere on the board
BP_I2S_BCK: J1.13 (BP_I2S_BCK); also elsewhere on the board
BP_I2S_LRCK: J1.15 (BP_I2S_LRCK); also elsewhere on the board
BP_I2S_SDOUT: J1.16 (BP_I2S_SDOUT); also elsewhere on the board
BP_LED_LOCK: J1.21 (BP_LED_LOCK); also elsewhere on the board
BP_LED_PEAK: J1.22 (BP_LED_PEAK); also elsewhere on the board
BP_SLOT0: J1.23 (BP_SLOT0); also elsewhere on the board
BP_SLOT1: J1.24 (BP_SLOT1); also elsewhere on the board
BP_SLOT2: J1.25 (BP_SLOT2); also elsewhere on the board
BP_UART_RX: J1.18 (BP_UART_RX); also elsewhere on the board
BP_UART_TX: J1.17 (BP_UART_TX); also elsewhere on the board
BP_nRESET: J1.19 (BP_nRESET); also elsewhere on the board

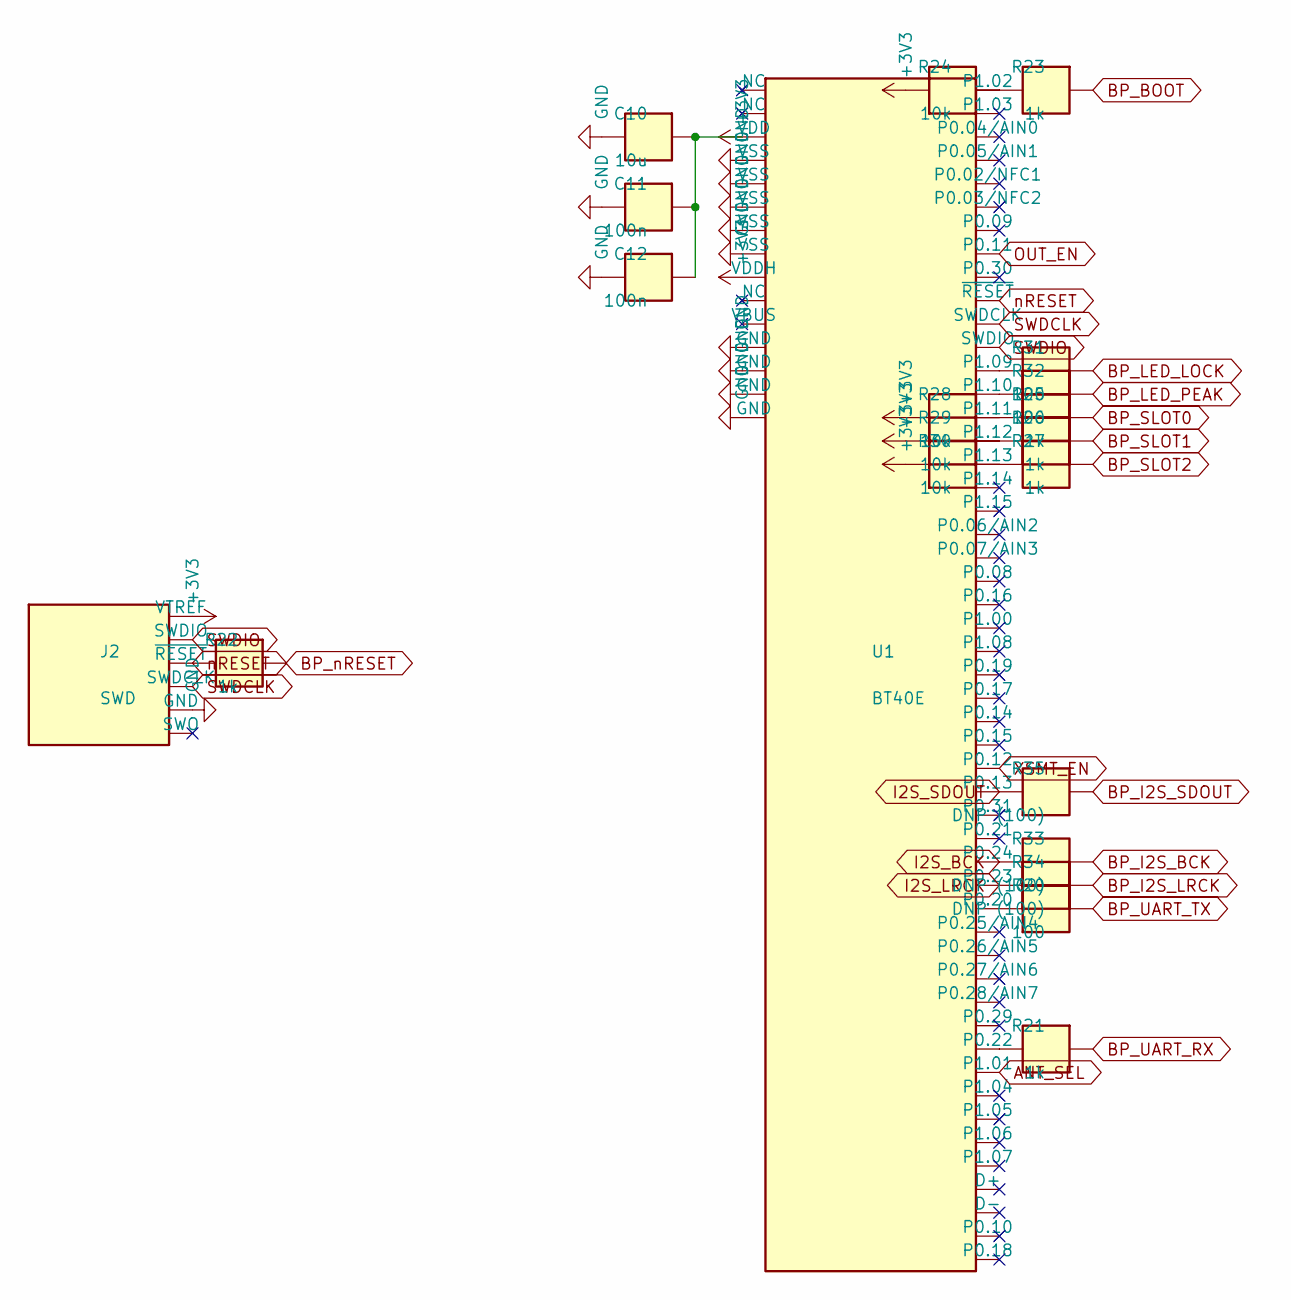
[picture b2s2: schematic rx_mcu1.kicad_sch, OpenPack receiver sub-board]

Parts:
C10: 10u; C_0603_1608Metric; MPN C_10u_0603_X5R
C11, C12: 100n; C_0402_1005Metric; MPN C_100n_0402
J2: SWD; Tag-Connect_TC2030-IDC-NL_2x03_P1.27mm_Vertical; MPN TC2030-pads
R20, R31, R32: 100; R_0402_1005Metric; MPN R_0402_1%
R21, R22, R23, R25, R26, R27: 1k; R_0402_1005Metric; MPN R_0402_1%
R24, R28, R29, R30: 10k; R_0402_1005Metric; MPN R_0402_1%
R33, R34, R35: DNP (100); R_0402_1005Metric; MPN DNP
U1: BT40E; Fanstel_BT40E; MPN BT40E

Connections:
ANT_SEL: U1.D6 (P1.01); also elsewhere on the board
BOOT: R23.2, R24.2, U1.1 (P1.02)
BP_BOOT: R23.1; also elsewhere on the board
BP_I2S_BCK: R33.2; also elsewhere on the board
BP_I2S_LRCK: R34.2; also elsewhere on the board
BP_I2S_SDOUT: R35.2; also elsewhere on the board
BP_LED_LOCK: R31.2; also elsewhere on the board
BP_LED_PEAK: R32.2; also elsewhere on the board
BP_SLOT0: R25.1; also elsewhere on the board
BP_SLOT1: R26.1; also elsewhere on the board
BP_SLOT2: R27.1; also elsewhere on the board
BP_UART_RX: R21.1; also elsewhere on the board
BP_UART_TX: R20.2; also elsewhere on the board
BP_nRESET: R22.1; also elsewhere on the board
I2S_BCK: R33.1, U1.C3 (P0.24); also elsewhere on the board
I2S_LRCK: R34.1, U1.C4 (P0.23); also elsewhere on the board
I2S_SDOUT: R35.1, U1.B6 (P0.13); also elsewhere on the board
LED_LOCK: R31.1, U1.Z0 (P1.09)
LED_PEAK: R32.1, U1.Z1 (P1.10)
OUT_EN: U1.12 (P0.11); also elsewhere on the board
SLOT0: R25.2, R28.2, U1.Z2 (P1.11)
SLOT1: R26.2, R29.2, U1.Z3 (P1.12)
SLOT2: R27.2, R30.2, U1.Z4 (P1.13)
SWDCLK: J2.4 (SWDCLK), U1.15 (SWDCLK)
SWDIO: J2.2 (SWDIO), U1.16 (SWDIO)
UART_RX: R21.2, U1.D5 (P0.22)
UART_TX: R20.1, U1.C5 (P0.20)
XSMT_EN: U1.B5 (P0.12); also elsewhere on the board
nRESET: J2.3 (~RESET), R22.2, U1.14 (~RESET)

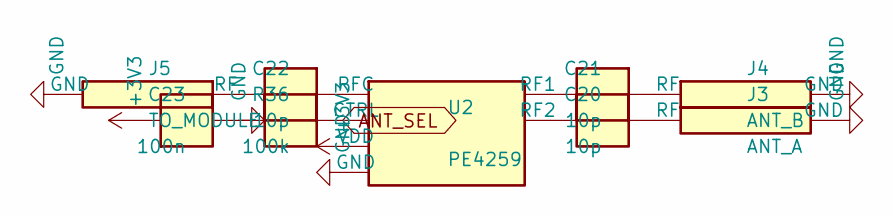
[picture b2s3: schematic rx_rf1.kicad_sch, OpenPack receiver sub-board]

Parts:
C20, C21, C22: 10p; C_0402_1005Metric; MPN C_10p_0402_C0G
C23: 100n; C_0402_1005Metric; MPN C_100n_0402
J3: ANT_A; U.FL_Hirose_U.FL-R-SMT-1_Vertical; MPN U.FL-R-SMT-1(10)
J4: ANT_B; U.FL_Hirose_U.FL-R-SMT-1_Vertical; MPN U.FL-R-SMT-1(10)
J5: TO_MODULE; U.FL_Hirose_U.FL-R-SMT-1_Vertical; MPN U.FL-R-SMT-1(10)
R36: 100k; R_0402_1005Metric; MPN R_0402_1%
U2: PE4259; SOT-363_SC-70-6; MPN PE4259-63

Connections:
ANT_SEL: R36.1, U2.4 (CTRL); also elsewhere on the board
RF_A: C20.1, J3.1 (RF)
RF_B: C21.1, J4.1 (RF)
RF_OUT: C22.2, J5.1 (RF)
SW_RF1: C21.2, U2.1 (RF1)
SW_RF2: C20.2, U2.3 (RF2)
SW_RFC: C22.1, U2.5 (RFC)
